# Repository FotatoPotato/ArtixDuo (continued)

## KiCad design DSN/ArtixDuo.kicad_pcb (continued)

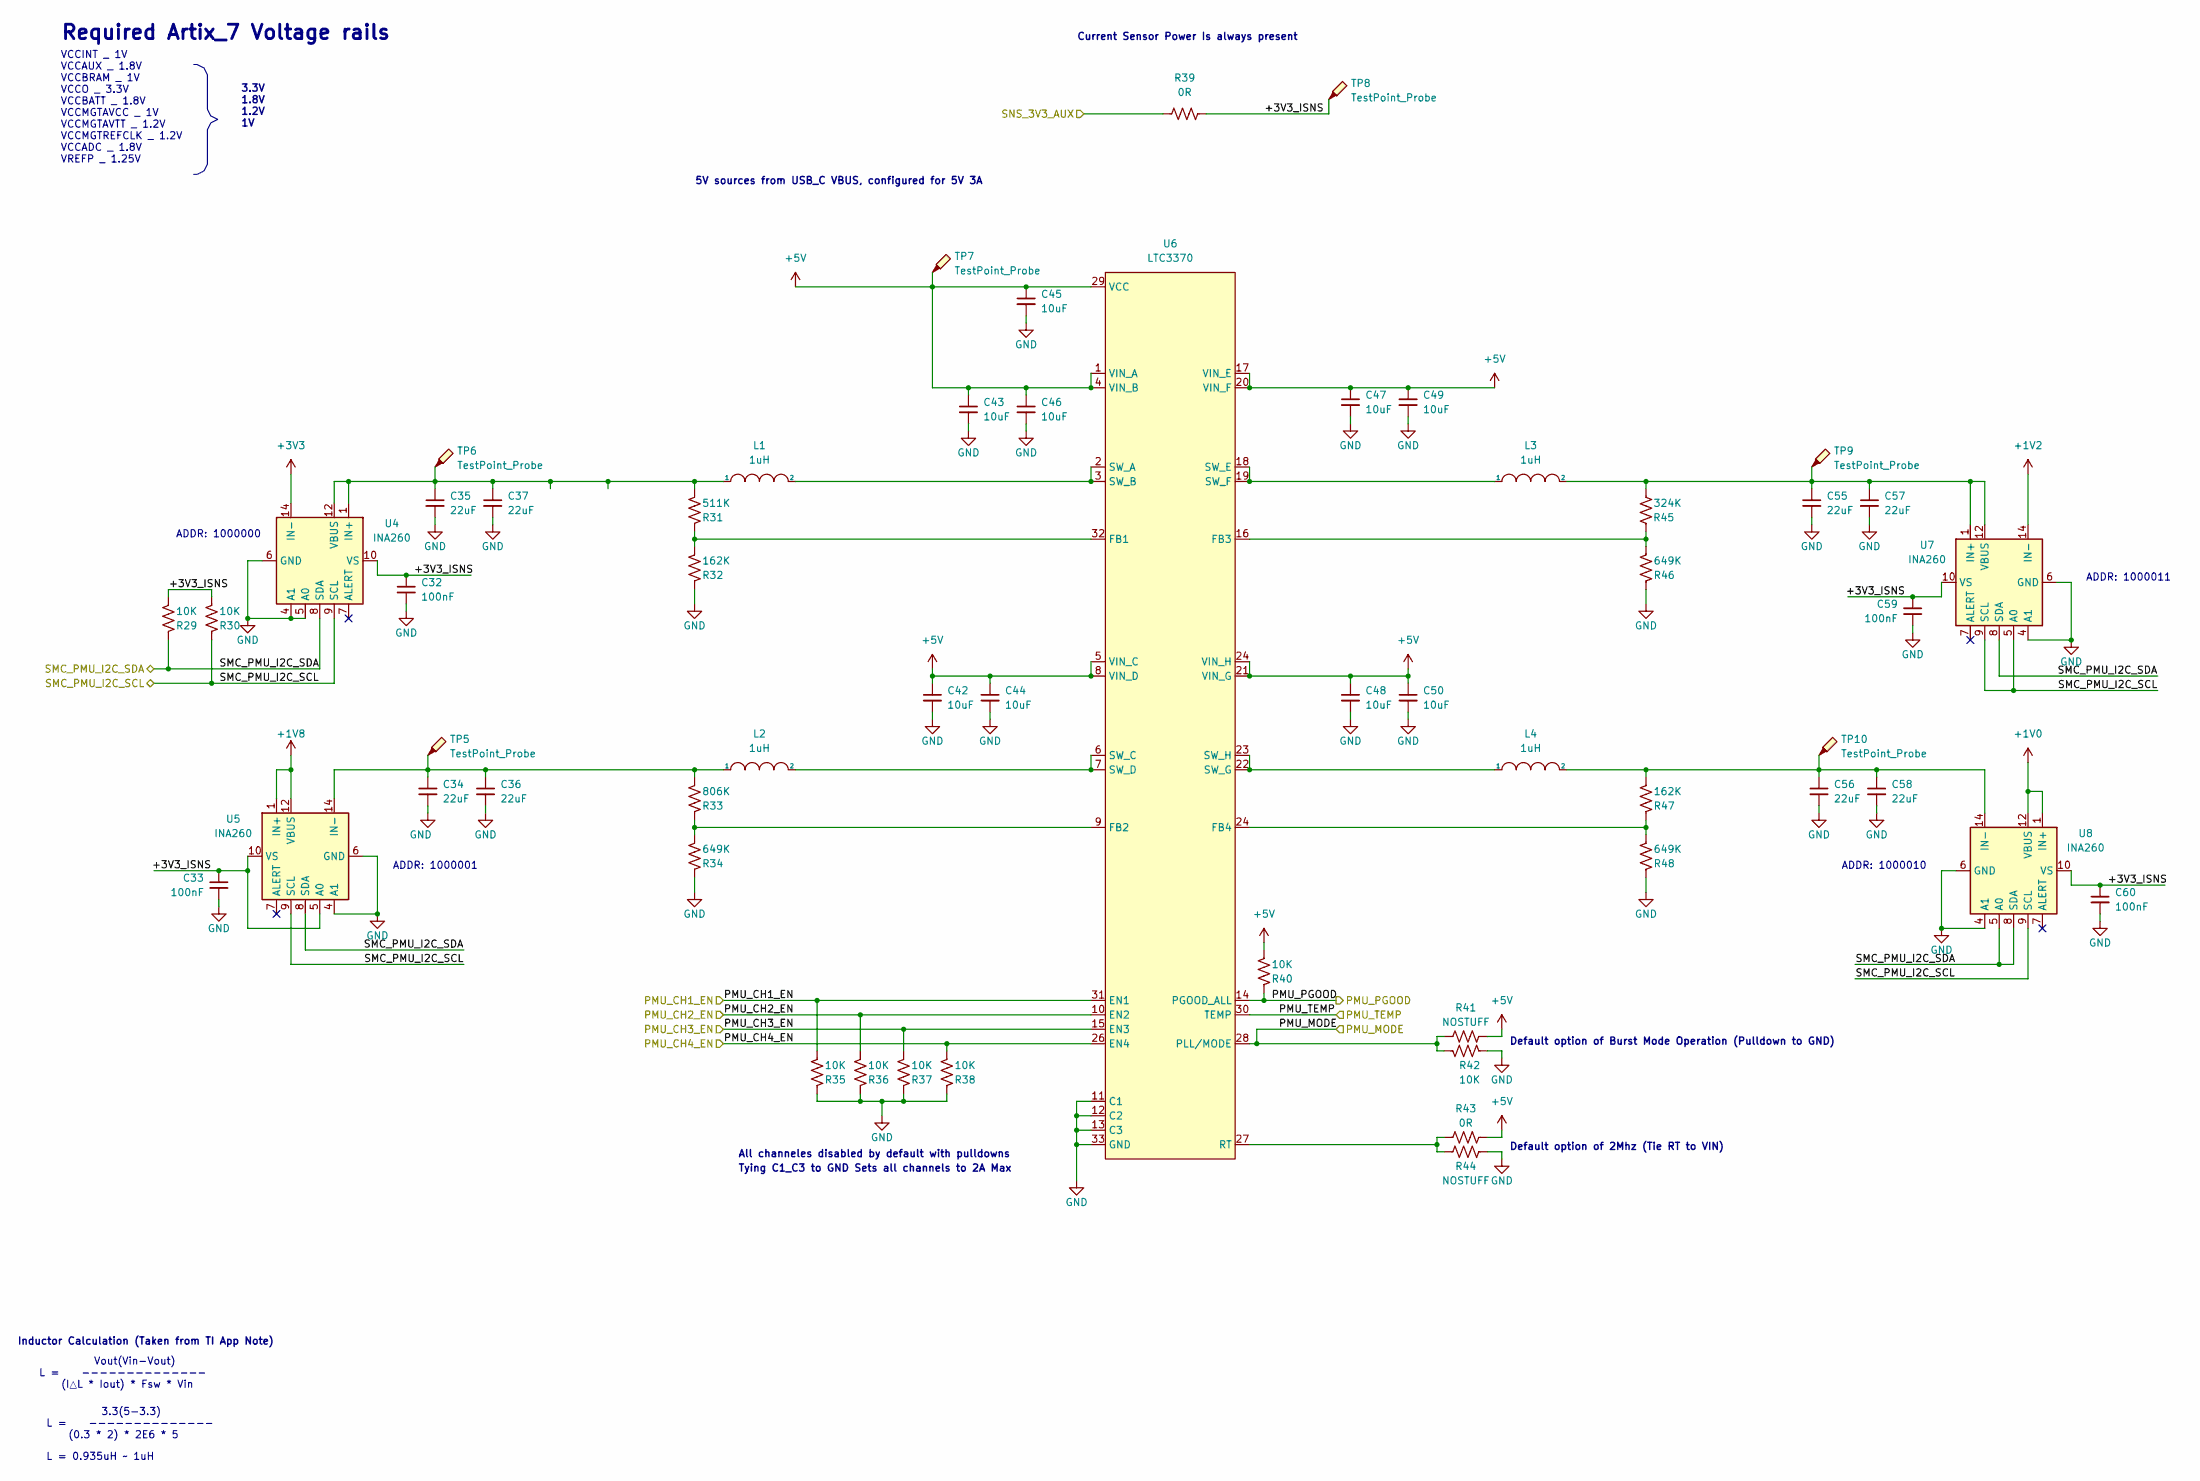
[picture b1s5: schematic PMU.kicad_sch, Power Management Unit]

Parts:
C32, C33, C59, C60: 100nF; C_0402_1005Metric; MFR PN GRM155R71H104ME14J
C34, C35, C36, C37, C55, C56, C57, C58: 22uF; C_1206_3216Metric; MFR PN GCM31CR71A226KE02L
C42, C43, C44, C45, C46, C47, C48, C49, C50: 10uF; C_0805_2012Metric; MFR PN GRM21BC71E106KE01K
L1, L2, L3, L4: 1uH; L_Coilcraft_XxL4020; MFR PN XFL4020-102MEC
R29, R30, R35, R36, R37, R38, R40, R42: 10K; R_0402_1005Metric; MFR PN RC0402FR-0710KP
R31: 511K; R_0402_1005Metric; MFR PN CRCW0402511KFKEDC
R32, R47: 162K; R_0402_1005Metric; MFR PN RC0402FR-07162KL
R33: 806K; R_0402_1005Metric; MFR PN RC0402FR-07806KL
R34, R46, R48: 649K; R_0402_1005Metric; MFR PN CRCW0402649KFKEDC
R39, R43: 0R; R_0402_1005Metric
R41, R44: NOSTUFF; R_0402_1005Metric
R45: 324K; R_0402_1005Metric; MFR PN RC0402FR-1324K3L
TP5, TP6, TP7, TP8, TP9, TP10: TestPoint_Probe; TestPoint_Loop_D1.80mm_Drill1.0mm_Beaded
U4, U5, U7, U8: INA260; TSSOP-16_4.4x5mm_P0.65mm
U6: LTC3370; QFN-32-1EP_5x5mm_P0.5mm_EP3.45x3.45mm_ThermalVias; MFR PN LTC3370IUH#PBF

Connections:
+1V0: U8.1 (IN+), U8.2 (IN+), U8.3 (IN+), U8.12 (VBUS); also elsewhere on the board
+1V2: U7.14 (IN-), U7.15 (IN-), U7.16 (IN-); also elsewhere on the board
+1V8: U5.1 (IN+), U5.2 (IN+), U5.3 (IN+), U5.12 (VBUS); also elsewhere on the board
+3.3VA: R39.1; also elsewhere on the board
+3V3: U4.14 (IN-), U4.15 (IN-), U4.16 (IN-); also elsewhere on the board
/TopSheet/PMU/+3V3_ISNS: C32.1, C33.1, C59.1, C60.1, R29.1, R30.1, R39.2, TP8.1, U4.10 (VS), U5.5 (A0), U5.10 (VS), U7.10 (VS), U8.10 (VS)
/TopSheet/PMU/PMU_CH1_EN: R35.1, U6.31 (EN1); also elsewhere on the board
/TopSheet/PMU/PMU_CH2_EN: R36.1, U6.10 (EN2); also elsewhere on the board
/TopSheet/PMU/PMU_CH3_EN: R37.1, U6.15 (EN3); also elsewhere on the board
/TopSheet/PMU/PMU_CH4_EN: R38.1, U6.26 (EN4); also elsewhere on the board
/TopSheet/PMU/PMU_MODE: R41.1, R42.1, U6.28 (PLL/MODE); also elsewhere on the board
/TopSheet/PMU/PMU_PGOOD: R40.2, U6.14 (PGOOD_ALL); also elsewhere on the board
/TopSheet/PMU/PMU_TEMP: U6.30 (TEMP); also elsewhere on the board
/TopSheet/PMU/SMC_PMU_I2C_SCL: R30.2, U4.9 (SCL), U5.9 (SCL), U7.5 (A0), U7.9 (SCL), U8.9 (SCL); also elsewhere on the board
/TopSheet/PMU/SMC_PMU_I2C_SDA: R29.2, U4.8 (SDA), U5.8 (SDA), U7.8 (SDA), U8.5 (A0), U8.8 (SDA); also elsewhere on the board
unnamed: C34.1, C36.1, L2.1, R33.1, TP5.1, U5.14 (IN-), U5.15 (IN-), U5.16 (IN-)
unnamed: C35.1, C37.1, L1.1, R31.1, TP6.1, U4.1 (IN+), U4.2 (IN+), U4.3 (IN+), U4.12 (VBUS)
unnamed: C55.1, C57.1, L3.2, R45.1, TP9.1, U7.1 (IN+), U7.2 (IN+), U7.3 (IN+), U7.12 (VBUS)
unnamed: C56.1, C58.1, L4.2, R47.1, TP10.1, U8.14 (IN-), U8.15 (IN-), U8.16 (IN-)
unnamed: L1.2, U6.2 (SW_A), U6.3 (SW_B)
unnamed: L2.2, U6.6 (SW_C), U6.7 (SW_D)
unnamed: L3.1, U6.18 (SW_E), U6.19 (SW_F)
unnamed: L4.1, U6.22 (SW_G), U6.23 (SW_H)
unnamed: R31.2, R32.1, U6.32 (FB1)
unnamed: R33.2, R34.1, U6.9 (FB2)
unnamed: R43.1, R44.1, U6.27 (RT)
unnamed: R45.2, R46.1, U6.16 (FB3)

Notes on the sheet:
5V sources from USB_C VBUS, configured for 5V 3A
Default option of 2Mhz (Tie RT to VIN)
ADDR: 1000001
Tying C1_C3 to GND Sets all channels to 2A Max
ADDR: 1000000
ADDR: 1000010
Required Artix_7 Voltage rails
Default option of Burst Mode Operation (Pulldown to GND)
3.3V 1.8V 1.2V 1V
Vout(Vin-Vout) L = -------------- (I△L * Iout) * Fsw * Vin
ADDR: 1000011
All channeles disabled by default with pulldowns
Current Sensor Power Is always present
L = 0.935uH ~ 1uH
VCCINT _ 1V VCCAUX _ 1.8V VCCBRAM _ 1V VCCO _ 3.3V VCCBATT _ 1.8V VCCMGTAVCC _ 1V VCCMGTAVTT _ 1.2V VCCMGTREFCLK _ 1.2V VCCADC _ 1.8V VREFP _ 1.25V
3.3(5-3.3) L = -------------- (0.3 * 2) * 2E6 * 5
Inductor Calculation (Taken from TI App Note)

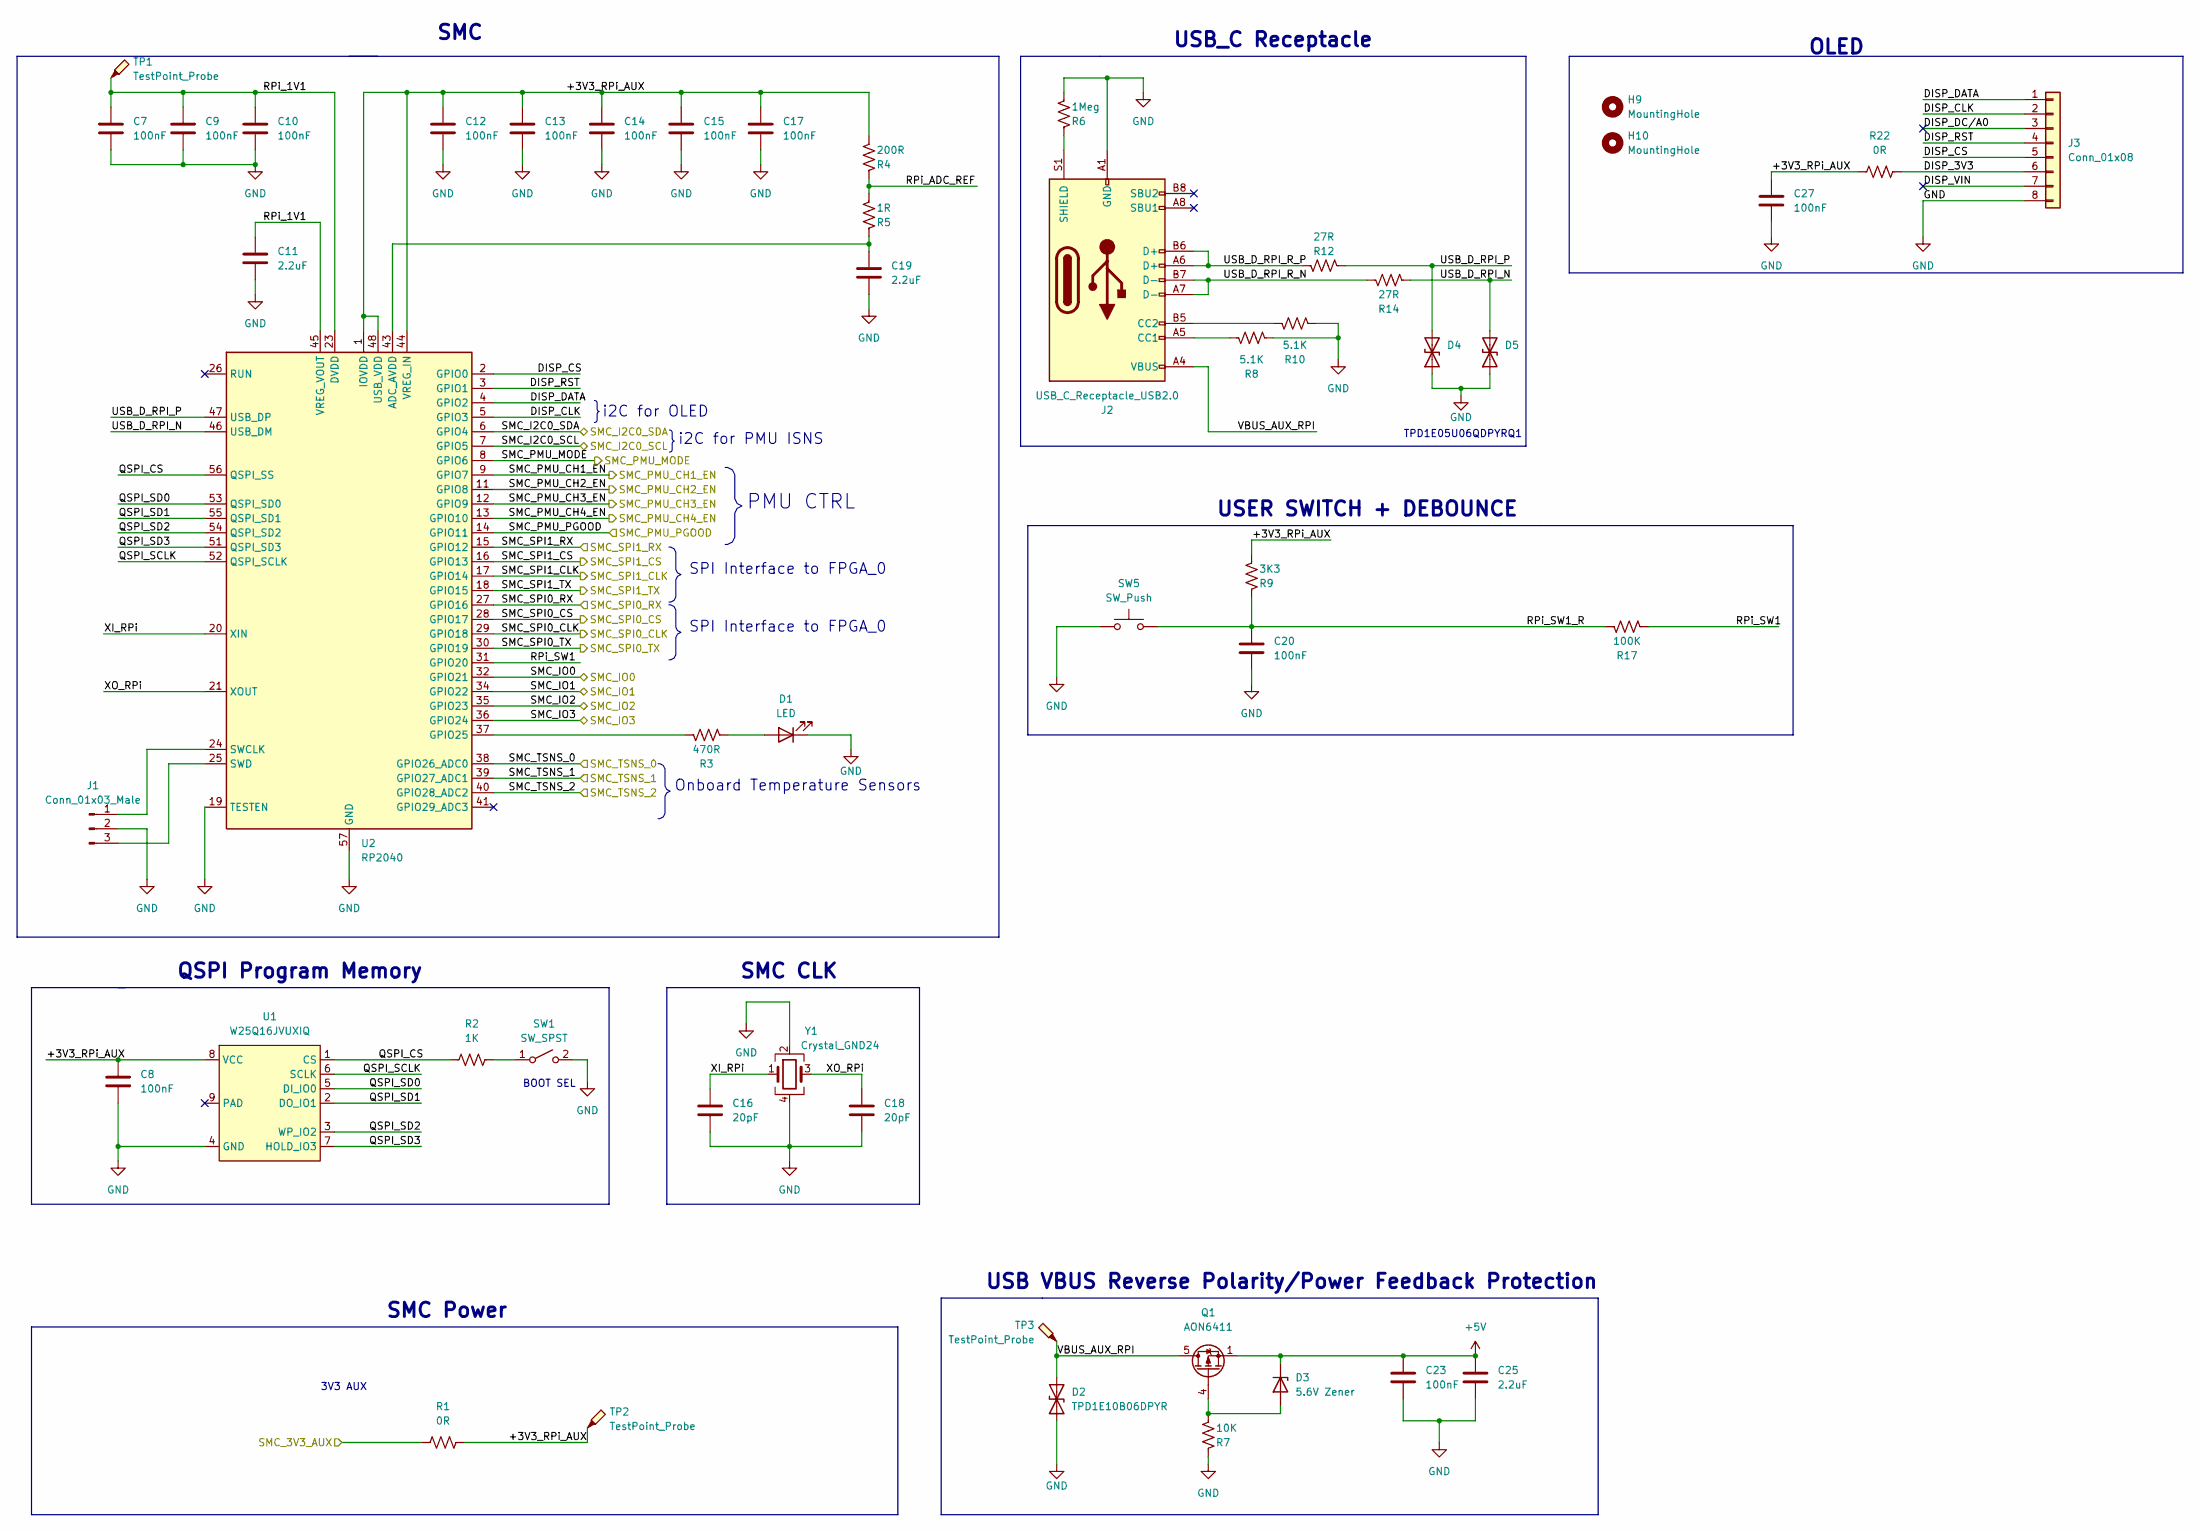
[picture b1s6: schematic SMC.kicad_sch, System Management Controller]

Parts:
C7, C8, C9, C10, C12, C13, C14, C15, C17, C20, C23, C27: 100nF; C_0402_1005Metric; MFR PN GRM155R71H104ME14J
C11, C19, C25: 2.2uF; C_0402_1005Metric; MFR PN GRT155R61E225KE13D
C16, C18: 20pF; C_0402_1005Metric; MFR PN GCM1555C1H200JA16D
D1: LED; LED_0603_1608Metric; MFR PN B1911PG--20D000514U1930
D2: TPD1E10B06DPYR; D_0402_1005Metric
D3: 5.6V Zener; D_SOD-123; MFR PN MMSZ5232BT1G
D4, D5: TPD1E05U06QDPYRQ1; D_0402_1005Metric
H9, H10: MountingHole; MountingHole_3.5mm
J1: Conn_01x03_Male; PinHeader_1x03_P2.54mm_Vertical
J2: USB_C_Receptacle_USB2.0; USB_C_Receptacle_GCT_USB4085
J3: Conn_01x08; PinHeader_1x08_P2.54mm_Vertical
Q1: AON6411; AO_DFN-8-1EP_5.55x5.2mm_P1.27mm_EP4.12x4.6mm
R1, R22: 0R; R_0402_1005Metric
R2: 1K; R_0402_1005Metric
R3: 470R; R_0402_1005Metric; MFR PN RC0402FR-07470RP
R4: 200R; R_0402_1005Metric; MFR PN RC0402FR-13200RL
R5: 1R; R_0402_1005Metric; MFR PN RC0402FR-071RL
R6: 1Meg; R_0402_1005Metric; MFR PN RC0402FR-071ML
R7: 10K; R_0402_1005Metric; MFR PN RC0402FR-0710KP
R8, R10: 5.1K; R_0402_1005Metric; MFR PN RC0402FR-075K1L
R9: 3K3; R_0402_1005Metric; MFR PN RC0402FR-073K3L
R12, R14: 27R; R_0402_1005Metric; MFR PN RC0402FR-0727RL
R17: 100K; R_0402_1005Metric; MFR PN RC0402FR-07100KL
SW1: SW_SPST; SW_SPST_B3U-1000P; MFR PN B3U-1000P
SW5: SW_Push; SW_SPST_B3SL-1022P; MFR PN B3SL-1022P
TP1, TP2, TP3: TestPoint_Probe; TestPoint_Loop_D1.80mm_Drill1.0mm_Beaded
U1: W25Q16JVUXIQ; WSON-8-1EP_4x4mm_P0.8mm_EP2.2x3mm_ThermalVias; MFR PN W25Q16JVUXIQ TR
U2: RP2040; QFN-56-1EP_7x7mm_P0.4mm_EP3.2x3.2mm
Y1: Crystal_GND24; Crystal_SMD_3225-4Pin_3.2x2.5mm; MFR PN 12M20P2/XT324-10/10

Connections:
+3.3VA: R1.1; also elsewhere on the board
/TopSheet/FPGA_0/FPGA_0_SPI_SMC_CS: U2.28 (GPIO17); also elsewhere on the board
/TopSheet/FPGA_0/FPGA_0_SPI_SMC_RX: U2.30 (GPIO19); also elsewhere on the board
/TopSheet/FPGA_0/FPGA_0_SPI_SMC_SCLK: U2.29 (GPIO18); also elsewhere on the board
/TopSheet/FPGA_0/FPGA_0_SPI_SMC_TX: U2.27 (GPIO16); also elsewhere on the board
/TopSheet/FPGA_0/SMC_IO0: U2.32 (GPIO21); also elsewhere on the board
/TopSheet/FPGA_0/SMC_IO1: U2.34 (GPIO22); also elsewhere on the board
/TopSheet/FPGA_0/TSNS_FPGA0: U2.39 (GPIO27_ADC1); also elsewhere on the board
/TopSheet/FPGA_1/FPGA_1_SPI_SMC_CS: U2.16 (GPIO13); also elsewhere on the board
/TopSheet/FPGA_1/FPGA_1_SPI_SMC_RX: U2.18 (GPIO15); also elsewhere on the board
/TopSheet/FPGA_1/FPGA_1_SPI_SMC_SCLK: U2.17 (GPIO14); also elsewhere on the board
/TopSheet/FPGA_1/FPGA_1_SPI_SMC_TX: U2.15 (GPIO12); also elsewhere on the board
/TopSheet/FPGA_1/SMC_IO2: U2.35 (GPIO23); also elsewhere on the board
/TopSheet/FPGA_1/SMC_IO3: U2.36 (GPIO24); also elsewhere on the board
/TopSheet/FPGA_1/TSNS_FPGA1: U2.40 (GPIO28_ADC2); also elsewhere on the board
/TopSheet/PMU/PMU_CH1_EN: U2.9 (GPIO7); also elsewhere on the board
/TopSheet/PMU/PMU_CH2_EN: U2.11 (GPIO8); also elsewhere on the board
/TopSheet/PMU/PMU_CH3_EN: U2.12 (GPIO9); also elsewhere on the board
/TopSheet/PMU/PMU_CH4_EN: U2.13 (GPIO10); also elsewhere on the board
/TopSheet/PMU/PMU_MODE: U2.8 (GPIO6); also elsewhere on the board
/TopSheet/PMU/PMU_PGOOD: U2.14 (GPIO11); also elsewhere on the board
/TopSheet/PMU/PMU_TEMP: U2.38 (GPIO26_ADC0); also elsewhere on the board
/TopSheet/PMU/SMC_PMU_I2C_SCL: U2.7 (GPIO5); also elsewhere on the board
/TopSheet/PMU/SMC_PMU_I2C_SDA: U2.6 (GPIO4); also elsewhere on the board
/TopSheet/SMC/+3V3_RPi_AUX: C8.1, C12.1, C13.1, C14.1, C15.1, C17.1, C27.1, R1.2, R4.1, R9.1, R22.1, TP2.1, U1.8 (VCC), U2.1 (IOVDD), U2.10 (IOVDD), U2.22 (IOVDD), U2.33 (IOVDD), U2.42 (IOVDD), U2.44 (VREG_IN), U2.48 (USB_VDD), U2.49 (IOVDD)
/TopSheet/SMC/DISP_3V3: J3.6, R22.2
/TopSheet/SMC/DISP_CLK: J3.2, U2.5 (GPIO3)
/TopSheet/SMC/DISP_CS: J3.5, U2.2 (GPIO0)
/TopSheet/SMC/DISP_DATA: J3.1, U2.4 (GPIO2)
/TopSheet/SMC/DISP_DC/A0: J3.3
/TopSheet/SMC/DISP_RST: J3.4, U2.3 (GPIO1)
/TopSheet/SMC/DISP_VIN: J3.7
/TopSheet/SMC/QSPI_CS: R2.1, U1.1 (CS), U2.56 (QSPI_SS)
/TopSheet/SMC/QSPI_SCLK: U1.6 (SCLK), U2.52 (QSPI_SCLK)
/TopSheet/SMC/QSPI_SD0: U1.5 (DI_IO0), U2.53 (QSPI_SD0)
/TopSheet/SMC/QSPI_SD1: U1.2 (DO_IO1), U2.55 (QSPI_SD1)
/TopSheet/SMC/QSPI_SD2: U1.3 (WP_IO2), U2.54 (QSPI_SD2)
/TopSheet/SMC/QSPI_SD3: U1.7 (HOLD_IO3), U2.51 (QSPI_SD3)
/TopSheet/SMC/RPi_1V1: C7.1, C9.1, C10.1, C11.1, TP1.1, U2.23 (DVDD), U2.45 (VREG_VOUT), U2.50 (DVDD)
/TopSheet/SMC/RPi_ADC_REF: R4.2, R5.1
/TopSheet/SMC/RPi_SW1: R17.2, U2.31 (GPIO20)
/TopSheet/SMC/RPi_SW1_R: C20.1, R9.2, R17.1, SW5.2
/TopSheet/SMC/USB_D_RPI_N: D5.2 (A2), R14.2, U2.46 (USB_DM)
/TopSheet/SMC/USB_D_RPI_P: D4.2 (A2), R12.2, U2.47 (USB_DP)
/TopSheet/SMC/USB_D_RPI_R_N: J2.A7 (D-), J2.B7 (D-), R14.1
/TopSheet/SMC/USB_D_RPI_R_P: J2.A6 (D+), J2.B6 (D+), R12.1
/TopSheet/SMC/VBUS_AUX_RPI: D2.2 (A2), J2.A4 (VBUS), J2.A9 (VBUS), J2.B4 (VBUS), J2.B9 (VBUS), Q1.5 (D), TP3.1
/TopSheet/SMC/XI_RPi: C16.1, U2.20 (XIN), Y1.1
/TopSheet/SMC/XO_RPi: C18.1, U2.21 (XOUT), Y1.3
unnamed: C19.1, R5.2, U2.43 (ADC_AVDD)
unnamed: D1.2 (A), R3.2
unnamed: D3.2 (A), Q1.4 (G), R7.1
unnamed: J1.1, U2.24 (SWCLK)
unnamed: J1.3, U2.25 (SWD)
unnamed: J2.A5 (CC1), R8.1
unnamed: J2.B5 (CC2), R10.1
unnamed: J2.S1 (SHIELD), R6.2
unnamed: R2.2, SW1.1 (A)
unnamed: R3.1, U2.37 (GPIO25)

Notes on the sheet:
SPI Interface to FPGA_0
TPD1E05U06QDPYRQ1
USB VBUS Reverse Polarity/Power Feedback Protection
PMU CTRL
USB_C Receptacle
USER SWITCH + DEBOUNCE
3V3 AUX
SMC Power
i2C for PMU ISNS
OLED
SMC
SPI Interface to FPGA_0
QSPI Program Memory
SMC CLK
i2C for OLED
Onboard Temperature Sensors
BOOT SEL

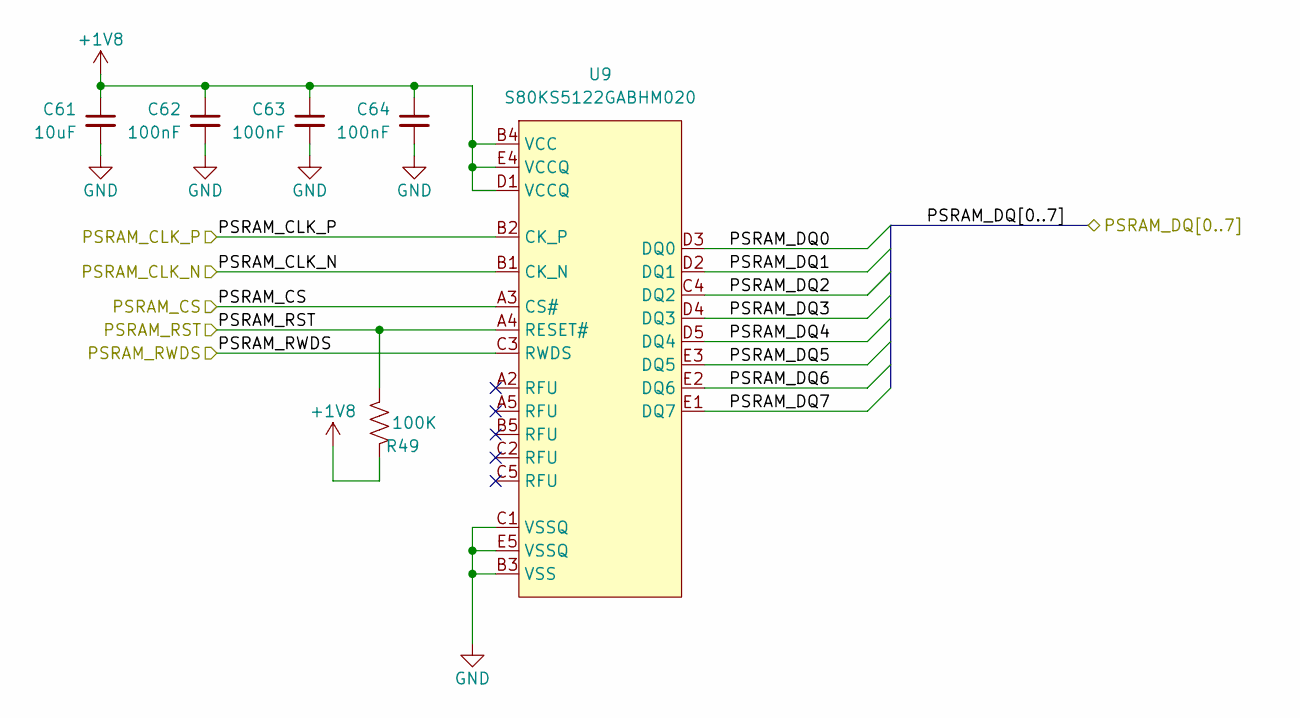
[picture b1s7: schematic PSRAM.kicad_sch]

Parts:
C61: 10uF; C_0603_1608Metric; MFR PN GRM185R60J106ME15J
C62, C63, C64: 100nF; C_0402_1005Metric; MFR PN GRM155R71H104ME14J
R49: 100K; R_0402_1005Metric; MFR PN RC0402FR-07100KL
U9: S80KS5122GABHM020; 24-BGA_6x8mm_5x5mm_ball_1.0mm_pitch; MFR PN S80KS5122GABHM020

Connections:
+1V8: C61.1, C62.1, C63.1, C64.1, R49.1, U9.B4 (VCC), U9.D1 (VCCQ), U9.E4 (VCCQ); also elsewhere on the board
/TopSheet/FPGA_0/FPGA_0_PSRAM_CLK_N: U9.B1 (CK_N); also elsewhere on the board
/TopSheet/FPGA_0/FPGA_0_PSRAM_CLK_P: U9.B2 (CK_P); also elsewhere on the board
/TopSheet/FPGA_0/FPGA_0_PSRAM_CS: U9.A3 (CS#); also elsewhere on the board
/TopSheet/FPGA_0/FPGA_0_PSRAM_D0: U9.D3 (DQ0); also elsewhere on the board
/TopSheet/FPGA_0/FPGA_0_PSRAM_D1: U9.D2 (DQ1); also elsewhere on the board
/TopSheet/FPGA_0/FPGA_0_PSRAM_D2: U9.C4 (DQ2); also elsewhere on the board
/TopSheet/FPGA_0/FPGA_0_PSRAM_D3: U9.D4 (DQ3); also elsewhere on the board
/TopSheet/FPGA_0/FPGA_0_PSRAM_D4: U9.D5 (DQ4); also elsewhere on the board
/TopSheet/FPGA_0/FPGA_0_PSRAM_D5: U9.E3 (DQ5); also elsewhere on the board
/TopSheet/FPGA_0/FPGA_0_PSRAM_D6: U9.E2 (DQ6); also elsewhere on the board
/TopSheet/FPGA_0/FPGA_0_PSRAM_D7: U9.E1 (DQ7); also elsewhere on the board
/TopSheet/FPGA_0/FPGA_0_PSRAM_RESET: R49.2, U9.A4 (RESET#); also elsewhere on the board
/TopSheet/FPGA_0/FPGA_0_PSRAM_RWDS: U9.C3 (RWDS); also elsewhere on the board

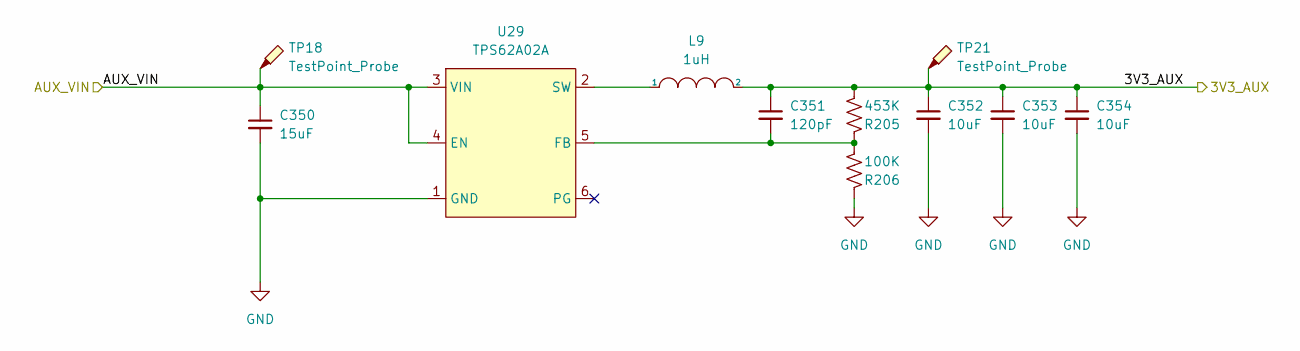
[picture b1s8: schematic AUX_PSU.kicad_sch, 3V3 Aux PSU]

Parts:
C350: 15uF; C_0805_2012Metric; MFR PN C2012X5R1V156M125AC
C351: 120pF; C_0402_1005Metric; MFR PN GRM1555C1H121JA01D
C352, C353, C354: 10uF; C_0805_2012Metric; MFR PN GRM31CR71E106KA12L
L9: 1uH; L_1008_2520Metric; MFR PN DFE252012F-1R0M=P2
R205: 453K; R_0402_1005Metric; MFR PN RC0402FR-07453KL
R206: 100K; R_0402_1005Metric; MFR PN RT0402FRE07100KL
TP18, TP21: TestPoint_Probe; TestPoint_Loop_D1.80mm_Drill1.0mm_Beaded
U29: TPS62A02A; SOT-563; MFR PN TPS62A02ADRLR

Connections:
+3.3VA: C351.1, C352.1, C353.1, C354.1, L9.2, R205.1, TP21.1; also elsewhere on the board
unnamed: C351.2, R205.2, R206.1, U29.5 (FB)
unnamed: L9.1, U29.2 (SW)

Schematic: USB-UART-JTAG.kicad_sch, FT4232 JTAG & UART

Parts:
C219, C220, C221, C223, C224, C228, C229, C231, C234, C235, C236, C237, C238, C239, C240, C241, C242: 100nF; C_0402_1005Metric; MFR PN GRM155R71H104ME14J
C222, C227, C230, C232, C233: 2.2uF; C_0402_1005Metric; MFR PN GRT155R61E225KE13D
C225, C226: 18pF; C_0402_1005Metric; MFR PN CC0402JRNPO9BN180
D28: TPD1E10B06DPYR; D_0402_1005Metric
D29, D31, D33, D35: LED RED; LED_0603_1608Metric; MFR PN 150060RS75000
D30, D32, D34, D36: LED GREEN; LED_0603_1608Metric; MFR PN 150060VS75000
D37: 5.6V Zener; D_SOD-123; MFR PN MMSZ5232BT1G
D38, D39: TPD1E05U06QDPYRQ1; D_0402_1005Metric
J27: USB_C_Receptacle_USB2.0; USB_C_Receptacle_GCT_USB4085
J28, J31: Conn_02x07_Odd_Even; PinHeader_2x07_P2.54mm_Vertical
J29, J30: Conn_01x03_Male; PinHeader_1x03_P2.54mm_Vertical
L6, L7: 100ohm; L_0402_1005Metric; MFR_PN 742792731
Q21: AON6411; AO_DFN-8-1EP_5.55x5.2mm_P1.27mm_EP4.12x4.6mm
R152: 1Meg; R_0402_1005Metric; MFR PN RC0402FR-071ML
R153, R154, R155, R156, R157, R158, R159, R160, R165: 2.2K; R_0402_1005Metric; MFR PN RT0402FRE072K2L
R161, R166, R169, R170, R171, R173, R174, R175, R177, R178, R179, R180, R181, R182, R183, R184, R185, R186, R187, R188, R189: 10K; R_0402_1005Metric; MFR PN RC0402FR-0710KP
R162, R163: 5.1K; R_0402_1005Metric; MFR PN RC0402FR-075K1L
R164, R167: 27R; R_0402_1005Metric; MFR PN RC0402FR-0727RL
R168: 0R; R_0402_1005Metric
R172: 12K; R_0402_1005Metric
R176: 1K; R_0402_1005Metric
TP13, TP14, TP17: TestPoint_Probe; TestPoint_Loop_D1.80mm_Drill1.0mm_Beaded
U15: 93LCxxB; SOIC-8_3.9x4.9mm_P1.27mm; MFR PN 93LC56B
U16: 74HC595; SSOP-16_5.3x6.2mm_P0.65mm; MFR PN SN74HC595PWRG4
U17: FT4232H; QFN-64-1EP_9x9mm_P0.5mm_EP4.35x4.35mm_ThermalVias
U18, U19: ADG794; QSOP-16_3.9x4.9mm_P0.635mm; MFR PN ADG794BRQZ
Y3: Crystal_GND24; Crystal_SMD_3225-4Pin_3.2x2.5mm; MFR PN ABM8AIG-12.000MHZ-1Z-T

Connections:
+3.3VA: R168.1; also elsewhere on the board
+3V3: C223.1, C239.1, J28.2, J31.2, R173.1, R174.1, R175.1, R177.1, R178.1, R179.1, R180.1, R181.1, R182.1, R183.1, R184.1, R185.1, R186.1, R187.1, R188.1, R189.1; also elsewhere on the board
/TopSheet/FPGA_0/FPGA_0_TCK: R182.2, U18.4 (D1); also elsewhere on the board
/TopSheet/FPGA_0/FPGA_0_TDI: R184.2, U18.7 (D2); also elsewhere on the board
/TopSheet/FPGA_0/FPGA_0_TDO: R186.2, U18.9 (D3); also elsewhere on the board
/TopSheet/FPGA_0/FPGA_0_TMS: R188.2, U18.12 (D4); also elsewhere on the board
/TopSheet/FPGA_0/FPGA_0_UART_RX: U17.38 (CDBUS0); also elsewhere on the board
/TopSheet/FPGA_0/FPGA_0_UART_TX: U17.39 (CDBUS1); also elsewhere on the board
/TopSheet/FPGA_1/FPGA_1_TCK: R183.2, U19.4 (D1); also elsewhere on the board
/TopSheet/FPGA_1/FPGA_1_TDI: R185.2, U19.7 (D2); also elsewhere on the board
/TopSheet/FPGA_1/FPGA_1_TDO: R187.2, U19.9 (D3); also elsewhere on the board
/TopSheet/FPGA_1/FPGA_1_TMS: R189.2, U19.12 (D4); also elsewhere on the board
/TopSheet/FPGA_1/FPGA_1_UART_RX: U17.48 (DDBUS0); also elsewhere on the board
/TopSheet/FPGA_1/FPGA_1_UART_TX: U17.52 (DDBUS1); also elsewhere on the board
/TopSheet/USB_UART_JTAG/EEPROM_CS: U15.1 (CS), U16.12 (RCLK), U17.63 (EECS)
/TopSheet/USB_UART_JTAG/EEPROM_DI: R165.2, R169.2, U15.3 (DI), U16.14 (SER), U17.61 (EEDATA)
/TopSheet/USB_UART_JTAG/EEPROM_DO: R165.1, R166.2, U15.4 (DO)
/TopSheet/USB_UART_JTAG/EEPROM_SCLK: R170.2, U15.2 (SCLK), U16.11 (SRCLK), U17.62 (EECLK)
/TopSheet/USB_UART_JTAG/FTDI_TCK_CH0: U17.16 (ADBUS0), U18.2 (S1A)
/TopSheet/USB_UART_JTAG/FTDI_TCK_CH1: U17.26 (BDBUS0), U19.2 (S1A)
/TopSheet/USB_UART_JTAG/FTDI_TDI_CH0: U17.17 (ADBUS1), U18.5 (S2A)
/TopSheet/USB_UART_JTAG/FTDI_TDI_CH1: U17.27 (BDBUS1), U19.5 (S2A)
/TopSheet/USB_UART_JTAG/FTDI_TDO_CH0: U17.18 (ADBUS2), U18.11 (S3A)
/TopSheet/USB_UART_JTAG/FTDI_TDO_CH1: U17.28 (BDBUS2), U19.11 (S3A)
/TopSheet/USB_UART_JTAG/FT_PWREN: R171.1, U16.13 (~OE), U17.60 (~PWREN)
/TopSheet/USB_UART_JTAG/FT_VCORE: C227.1, C230.1, C231.1, C234.1, C235.1, TP17.1, U17.12 (VCORE), U17.37 (VCORE), U17.49 (VREGOUT), U17.64 (VCORE)
/TopSheet/USB_UART_JTAG/JTAG_H_CH0_TCK: J28.4, R177.2, U18.3 (S1B)
/TopSheet/USB_UART_JTAG/JTAG_H_CH0_TDI: J28.6, R175.2, U18.6 (S2B)
/TopSheet/USB_UART_JTAG/JTAG_H_CH0_TDO: J28.8, R174.2, U18.10 (S3B)
/TopSheet/USB_UART_JTAG/JTAG_H_CH0_TMS: J28.10, R173.2, U18.13 (S4B)
/TopSheet/USB_UART_JTAG/JTAG_H_CH1_TCK: J31.4, R181.2, U19.3 (S1B)
/TopSheet/USB_UART_JTAG/JTAG_H_CH1_TDI: J31.6, R180.2, U19.6 (S2B)
/TopSheet/USB_UART_JTAG/JTAG_H_CH1_TDO: J31.8, R179.2, U19.10 (S3B)
/TopSheet/USB_UART_JTAG/JTAG_H_CH1_TMS: J31.10, R178.2, U19.13 (S4B)
/TopSheet/USB_UART_JTAG/USB_D_PROG_N: D39.2 (A2), R167.2, U17.7 (DM)
/TopSheet/USB_UART_JTAG/USB_D_PROG_P: D38.2 (A2), R164.2, U17.8 (DP)
/TopSheet/USB_UART_JTAG/USB_D_PROG_R_N: J27.A7 (D-), J27.B7 (D-), R167.1
/TopSheet/USB_UART_JTAG/USB_D_PROG_R_P: J27.A6 (D+), J27.B6 (D+), R164.1
/TopSheet/USB_UART_JTAG/VBUS_AUX_PROG: D28.2 (A2), J27.A4 (VBUS), J27.A9 (VBUS), J27.B4 (VBUS), J27.B9 (VBUS), Q21.5 (D), TP13.1
unnamed: C225.2, U17.2 (OSCI), Y3.3
unnamed: C226.2, U17.3 (OSCO), Y3.1
unnamed: C228.1, C232.1, L6.2, U17.9 (VPLL)
unnamed: C229.1, C233.1, L7.2, U17.4 (VPHY)
unnamed: D29.2 (A), R153.1
unnamed: D30.2 (A), R154.1
unnamed: D31.2 (A), R155.1
unnamed: D32.2 (A), R156.1
unnamed: D33.2 (A), R157.1
unnamed: D34.2 (A), R158.1
unnamed: D35.2 (A), R159.1
unnamed: D36.2 (A), R160.1
unnamed: D37.2 (A), Q21.4 (G), R161.1
unnamed: J27.A5 (CC1), R162.1
unnamed: J27.B5 (CC2), R163.1
unnamed: J27.S1 (SHIELD), R152.2
unnamed: J29.2, U18.1 (IN)
unnamed: J30.2, U19.1 (IN)
unnamed: R153.2, U16.15 (QA)
unnamed: R154.2, U16.1 (QB)
unnamed: R155.2, U16.2 (QC)
unnamed: R156.2, U16.3 (QD)
unnamed: R157.2, U16.4 (QE)
unnamed: R158.2, U16.5 (QF)
unnamed: R159.2, U16.6 (QG)
unnamed: R160.2, U16.7 (QH)
unnamed: R172.1, U17.6 (REF)
unnamed: R176.2, U17.14 (~RESET)

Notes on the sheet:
TPD1E05U06QDPYRQ1
FPGA_1 UART
FPGA_0 JTAG Header
FR4232 EEPROM
FT4232 Power
FPGA_0 JTAG
FPGA_0 UART
JTAG POWER FROM PMU, NOT FT VCCIO
JTAG GOING TO FPGA TO BE PULLED UP BY FPGA 3V3 SOURCE NOT FT VCCIO
LED RX/TX STATUS
MUX For switching from Header to FT4232
ADBUS _> JTAG_0 BDBUS _> JTAG_1 CDBUS _> UART_0 DDBUS _> UART_1
USB VBUS Reverse Polarity/Power Feedback Protection
UART/JTAG USB
